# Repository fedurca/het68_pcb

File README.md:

# het68_pcb

Zadání a KiCad návrh PCB pro **het68** (akustická detekce dronů).

Aktuální verze: **[v4.9.0](https://github.com/fedurca/het68_pcb/releases/tag/v4.9.0)** — viz [CHANGELOG.md](CHANGELOG.md). Kusovník sady: [kicad/BOM_KIT.csv](kicad/BOM_KIT.csv). Po deskách: [kicad/BOM_v4.csv](kicad/BOM_v4.csv).

Firmware a geometrie pole: [fedurca/het68](https://github.com/fedurca/het68). Zadání: [docs/ZADANI_PCB.md](docs/ZADANI_PCB.md). Projekty v KiCadu: [kicad/README.md](kicad/README.md).

## Co to je

v4 je sada **Core 6L + vyměnitelná silová deska + šest satelitů**. Na měď nepřijde 230 V, 22 kV ani 110 kV.

**Core** (`kicad/het68-core`) nese nativní RP2350B, flash, PSRAM, USB-C, šest RJ45 s LVDS, piezo, env senzor, ADXL355, stavovou SK6812, tlačítka RESET / BOOT / USER a `J_MESH` na Heltec WiFi LoRa 32 V3 (868 MHz). MeshCore běží na Heltecu, takže uzel v síti žije, i když DSP spí. `WAKE_DSP` zapíná `+3V3_DIG`.

**Silová deska** má tři SKU se stejným interconnectem 2×10: NN (multiplex CT), VN (silnější GDT/TVS), VVN (harvest CT + Rogowski). Společný front-end je jen sekundár: GDT, TVS, LC, burden, crowbar, MPPT, článek 21700 (LiFePO4/LTO), 5 V a vždyživý `+3V3_RF`.

**Satelit** je šest destiček 6L. Ven z desky kouká jen akustický otvor T5848 a kruh **8× SK6812**. Tělo mikrofonu, RJ45 a ostatní elektronika jsou na druhé straně. Režim linky volí propojka na satelitu: diferenciální LVDS, jednostranných 3,3 V, nebo 1,8 V přímo na T5848. Mapa [`docs/PINOUT_SAT_v4.csv`](docs/PINOUT_SAT_v4.csv).

## Prototyp

Náhledy Core a satelitu jsou z v4.9.0. Ukazují svislý RJ45 a na zadní straně satelitu propojky režimu. Silová deska je náhled z v4.6.0.

Měď: [Core](docs/img/v490/core-top.svg) · [satelit ven](docs/img/v490/sat-front.svg) · [satelit zadek](docs/img/v490/sat-back.svg) · [silová](docs/img/v460/pwr-nn-top.svg). Maska venkovní strany satelitu: [SVG](docs/img/v490/sat-front-mask.svg). Schémata: [Core](docs/img/v490/core-sch.pdf) · [satelit](docs/img/v490/sat-sch.pdf) · [silová](docs/img/v460/pwr-nn-sch.pdf). Gerbery a nastavení formuláře: [`kicad/jlc/`](kicad/jlc/) · [NASTAVENI.md](kicad/jlc/NASTAVENI.md).

## Vyrobitelnost

Na měď nejde 230 V / 22 kV / 110 kV. Gerbery z `kicad-cli` v `kicad/*/fab/`. TPV: JLC / standardní výroba, ENIG na 6L, ≥ 0603, ne BGA. QFN-80 0,4 mm a LGA chtějí ENIG.

| Deska | Rozměr | ERC error | DRC | Objednat? |
|---|---|---|---|---|
| Core | 160 × 100 mm, 6L Faraday, ENIG | 0 | 0 zkratů, 0 mezer, 43 otevřených párů | ne |
| Satelit | 50 × 80 mm, 6L, ven jen LED a port | 0 | 0 zkratů, 19 otevřených párů (dva jsou rohy zemních zón) | ne, dokud nejsou dotažené jack, WS a OE |
| Silová NN/VN/VVN | 140 × 80 mm, 2L 70 µm | 0 | 0 zkratů, otevřené páry 30 / 36 / 26 | ne jako hotový zdroj |

Schémata jsou elektricky uzavřená (ERC 0 chyb). Core vrtá prokov 0,30/0,15 mm, což se do rozteče QFN 0,40 mm vejde, a L4 pod procesorem je plocha `+3V3_DIG`. DRC Core nemá zkrat ani mezeru. Otevřených je 43 párů. Část z nich je původní únik z prstence QFN, zbytek jsou vývody svislého RJ45 a stopy, které nová rozteč pinů přerušila. Satelit nemá zkrat. Vzdušné zůstávají `LED` a část `SD` u jacku, `OE`, krátká mezera `SD_3V3` u `U5` a sítě slovního taktu (`WS_LVDS`, `WS_P`, `WS_T`, `WS_N`). Dva záznamy jsou rohy zemních zón.

## VF / EMC (silné rušení)

- 6L Faraday: L2/L5 souvislá GND. Na Core je L4 jedna plocha `+3V3_DIG`. Silové desky mají L4 rozdělené. Stitch po obvodu.
- Diferenciální režim vozí I²S po LVDS (T568B páry). Propojka na satelitu umí i jednostranných 3,3 V a 1,8 V. Stínění je na GND na Core i na satelitu.
- CMC na SCK, WS i SD na obou koncích; nízko-kapacitní TVS napříč párem; 100 Ω u přijímače (SN65LVDS2 / SN65LVDS32 nemají vnitřní zakončení).
- Ferit 600 Ω na 3V3 každého jacku a na satelitu za PPTC.
- Krystal 12 MHz s C0G 15 pF (ne X7R 100 nF). Sériové 33 Ω na I²S u MCU, 22 Ω + ESD na UART MeshCore.
- Rádio (SX1262) je na Heltecu mimo DSP; `+3V3_RF` je vždyživé a oddělené od hradlovaného `+3V3_DIG`.

## Co je ještě potřeba

1. **Firmware.** DSP = RP2350B. MeshCore na Heltecu: `Heltec_lora32_v3`, UART GPIO5/6, WAKE GPIO7.
2. **Dokončit střední piny QFN-80** (QSPI SD2/SD3, část LED, SWD, UART) a zbylé LVDS páry. Silová deska má překryté pady z rozmístění.
3. **Heltec je lab.** ~40–80 mA. Stamp nRF52 později. LTO povinná, minimální SOC repeateru 30 %.
4. **110 kV.** Žádný externí kabel ze sféry. Anténa U.FL do slotu u stampu.
5. **RGB na 3,3 V.** Firmware svítí nejvýš dvěma pixely naráz.

## Sestava

Kleště / CT jsou na jednom izolovaném vodiči. Na desku jde jen sekundár (burden, LC, crowbar). Panel a článek LiFePO4/LTO jsou u silové desky, výstup `+5V_ALWAYS` jde na Core, šest satelitů je na RJ45.

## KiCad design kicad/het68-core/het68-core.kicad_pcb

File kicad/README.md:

# het68 — KiCad (v4.1.0)

Náhledy a kontext: [README](../README.md) repozitáře.

v4 kreslí **Core 6L**, tři silové SKU a satelit LVDS.

| Projekt | Deska | Vrstvy | Obrys |
|---|---|---|---|
| [het68-core](het68-core/het68-core.kicad_pro) | RP2350B + J_MESH Heltec V3 + 6× RJ45 LVDS | 6 Faraday | 160 × 100 mm |
| [het68-sat](het68-sat/het68-sat.kicad_pro) | satelit 6L LVDS + T5848 + 8× SK6812 | 6 Faraday, ENIG | 50 × 80 mm |
| [het68-pwr-nn](het68-pwr-nn/het68-pwr-nn.kicad_pro) | silová NN, multiplex CT | 2, 70 µm | 140 × 80 mm |
| [het68-pwr-vn](het68-pwr-vn/het68-pwr-vn.kicad_pro) | silová VN, 15KP | 2, 70 µm | 140 × 80 mm |
| [het68-pwr-vvn](het68-pwr-vvn/het68-pwr-vvn.kicad_pro) | silová VVN, Rogowski | 2, 70 µm | 140 × 80 mm |

Generátor: `kicad/tools/gen_v4.py` (Python z KiCadu). 6L stackup: `kicad/tools/route6.py`. Kusovník sady: [`BOM_KIT.csv`](BOM_KIT.csv).

## Zapojení Core

- RP2350B QFN-80, W25Q128 SOIC-8, APS6404L SOIC-8, USB-C, krystal 12 MHz + C0G 15 pF.
- `+3V3_DIG` a `+1V8_AUDIO` hradluje `WAKE_DSP` (Heltec GPIO7). `+5V_ALWAYS` / `+3V3_RF` vždyživé.
- `J_MESH` 1×8: GND, 5V, UART TX/RX (22 Ω + ESD), WAKE_DSP, DSP_AWAKE, RST NC, rezerva. Stamp DNP paralelně na pinech 1–6.
- Šest svislých RJ45, zástrčka kolmo z přední strany. Mapa [`docs/PINOUT_SAT_v4.csv`](../docs/PINOUT_SAT_v4.csv). CMC na SCK/WS/SD, 100 Ω u RX SD, ferit na 3V3.
- GPIO: [`docs/PINOUT.csv`](../docs/PINOUT.csv).
- Interconnect: [`docs/INTERCONNECT_v4.md`](../docs/INTERCONNECT_v4.md).
- L1 SMT+GND, L2 GND, L3 stripline, L4 souvislá `+3V3_DIG`, L5 GND, L6 pomalé+GND. Prokov 0,30/0,15 mm. Stitch po obvodu.

## Silová deska

Jen sekundár CT/Rogowski. GDT, TVS, LC, THT burden 100 Ω, crowbar ~25 V, USB-C lab, CN3791, LiFePO4, boost 5 V, LDO 3V3_RF, INA3221, PT1000. NN má MOSFET multiplex burdenu. VN 15KP. VVN Rogowski + MCP6001.

## Satelit

6L Faraday. RJ45 stojí ze zadní strany, osa zástrčky je kolmá k desce. Režim linky volí jedna vodorovná propojka. `JP_SCK`, `JP_WS` a `JP_SD` jsou hřebínky 2×3 na spodní straně, pin 1 (čtvercový) je severovýchodní. Severní řádek je diferenciální LVDS, prostřední je jednostranných 3,3 V přes `TXS0104E`, jižní je 1,8 V přímo na T5848. `JP_T*` jen u diferenciálního režimu (100 Ω). `JP_SDN` 1–2 je záporný vývod budiče, 2–3 dává zápornou žílu na zem. `JP_OE` se nasazuje jen v režimu 1,8 V a vypne překladač. T5848 zůstává na 1,62–1,98 V. Stínění RJ45 je na satelitu na GND. DRC desky je bez zkratů. Vzdušné zůstávají vývod `LED` a část `SD` u jacku, `OE`, krátká mezera `SD_3V3` u `U5`, `WS_LVDS`, `WS_P`, `WS_T` a `WS_N`. Náhled je v [`docs/img/v490/`](../docs/img/v490/). ENIG, ≥ 0603.

## Výroba

Gerbery z `kicad-cli pcb export gerbers` (ne `WriteDRCReport`). Core a satelit 6L ENIG u JLC. Silová 2L 70 µm.

v4.1.0: schémata elektricky uzavřená, BoM sady, 3D náhledy. Spoje 6L jsou v4.2.0.

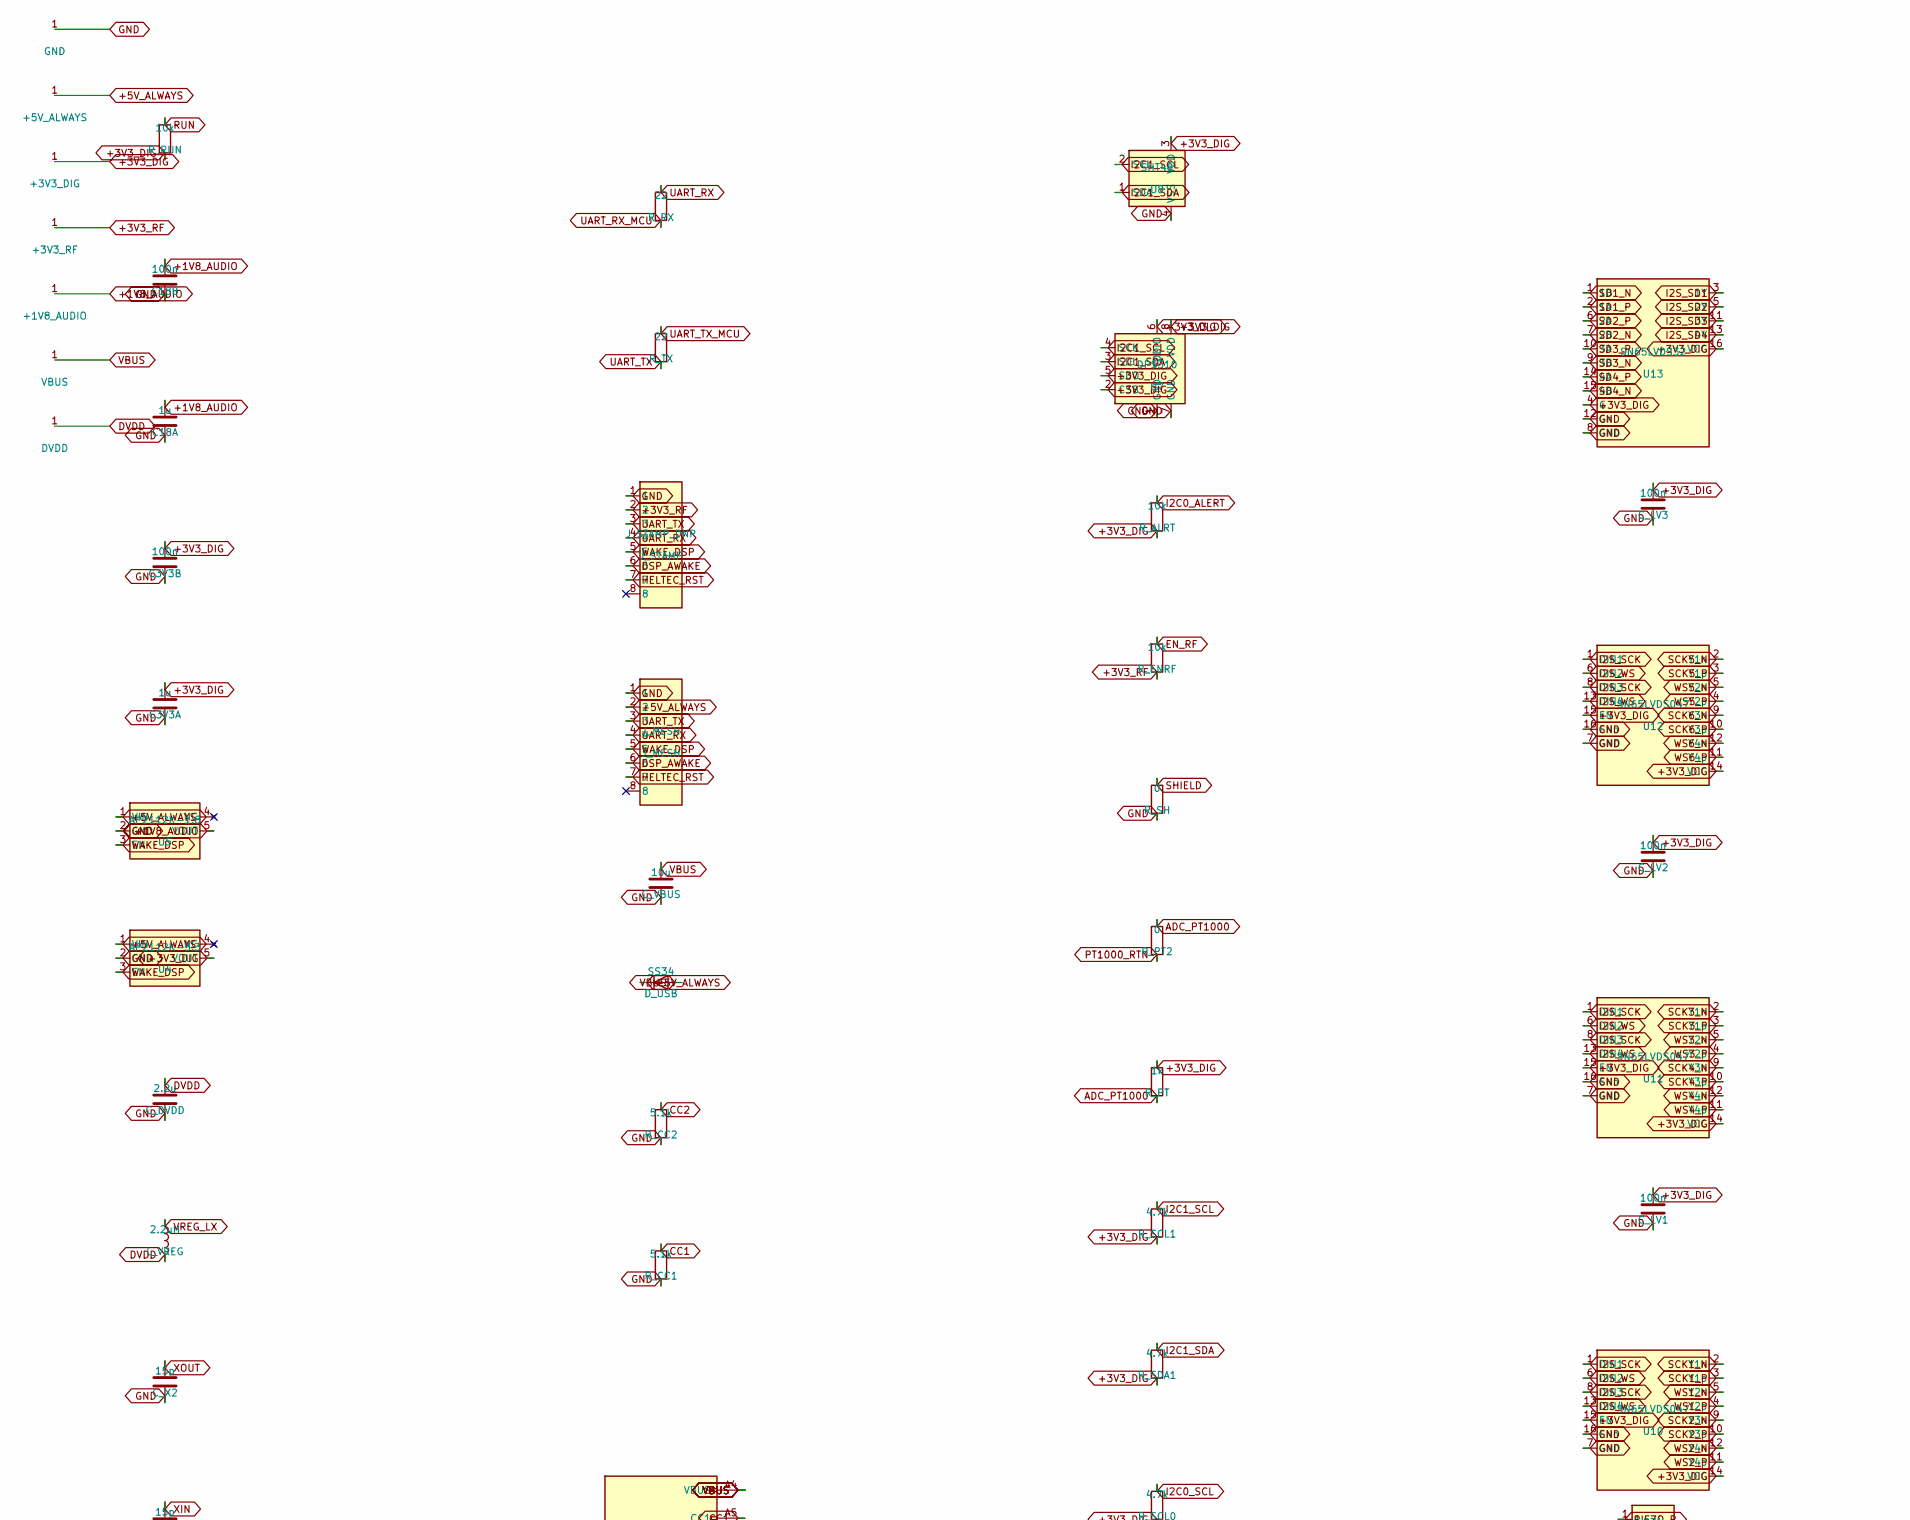
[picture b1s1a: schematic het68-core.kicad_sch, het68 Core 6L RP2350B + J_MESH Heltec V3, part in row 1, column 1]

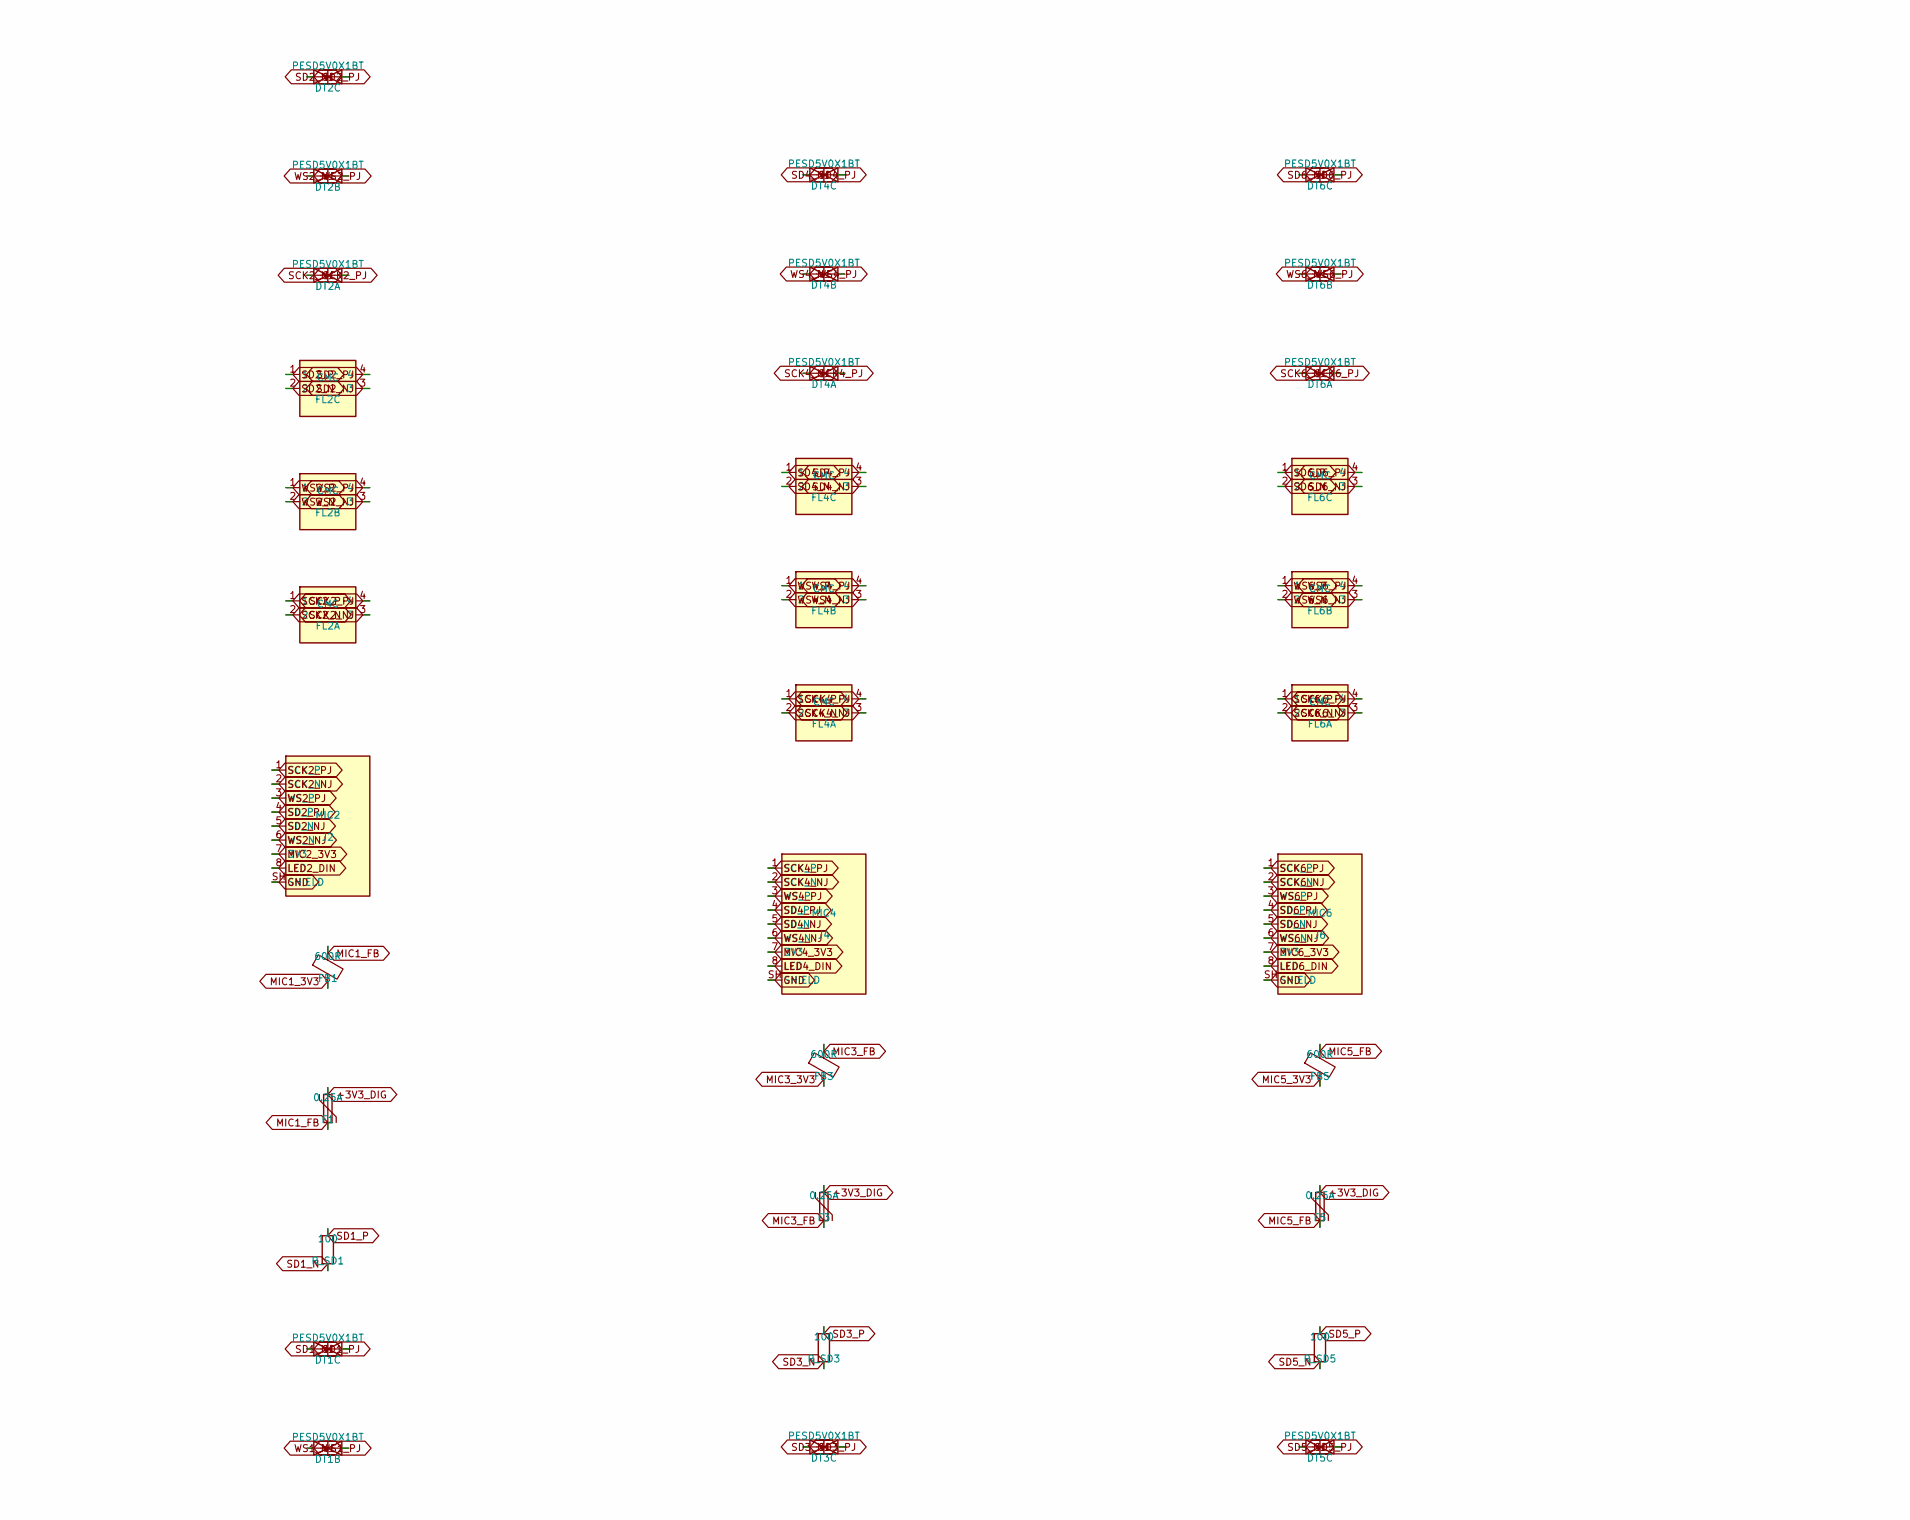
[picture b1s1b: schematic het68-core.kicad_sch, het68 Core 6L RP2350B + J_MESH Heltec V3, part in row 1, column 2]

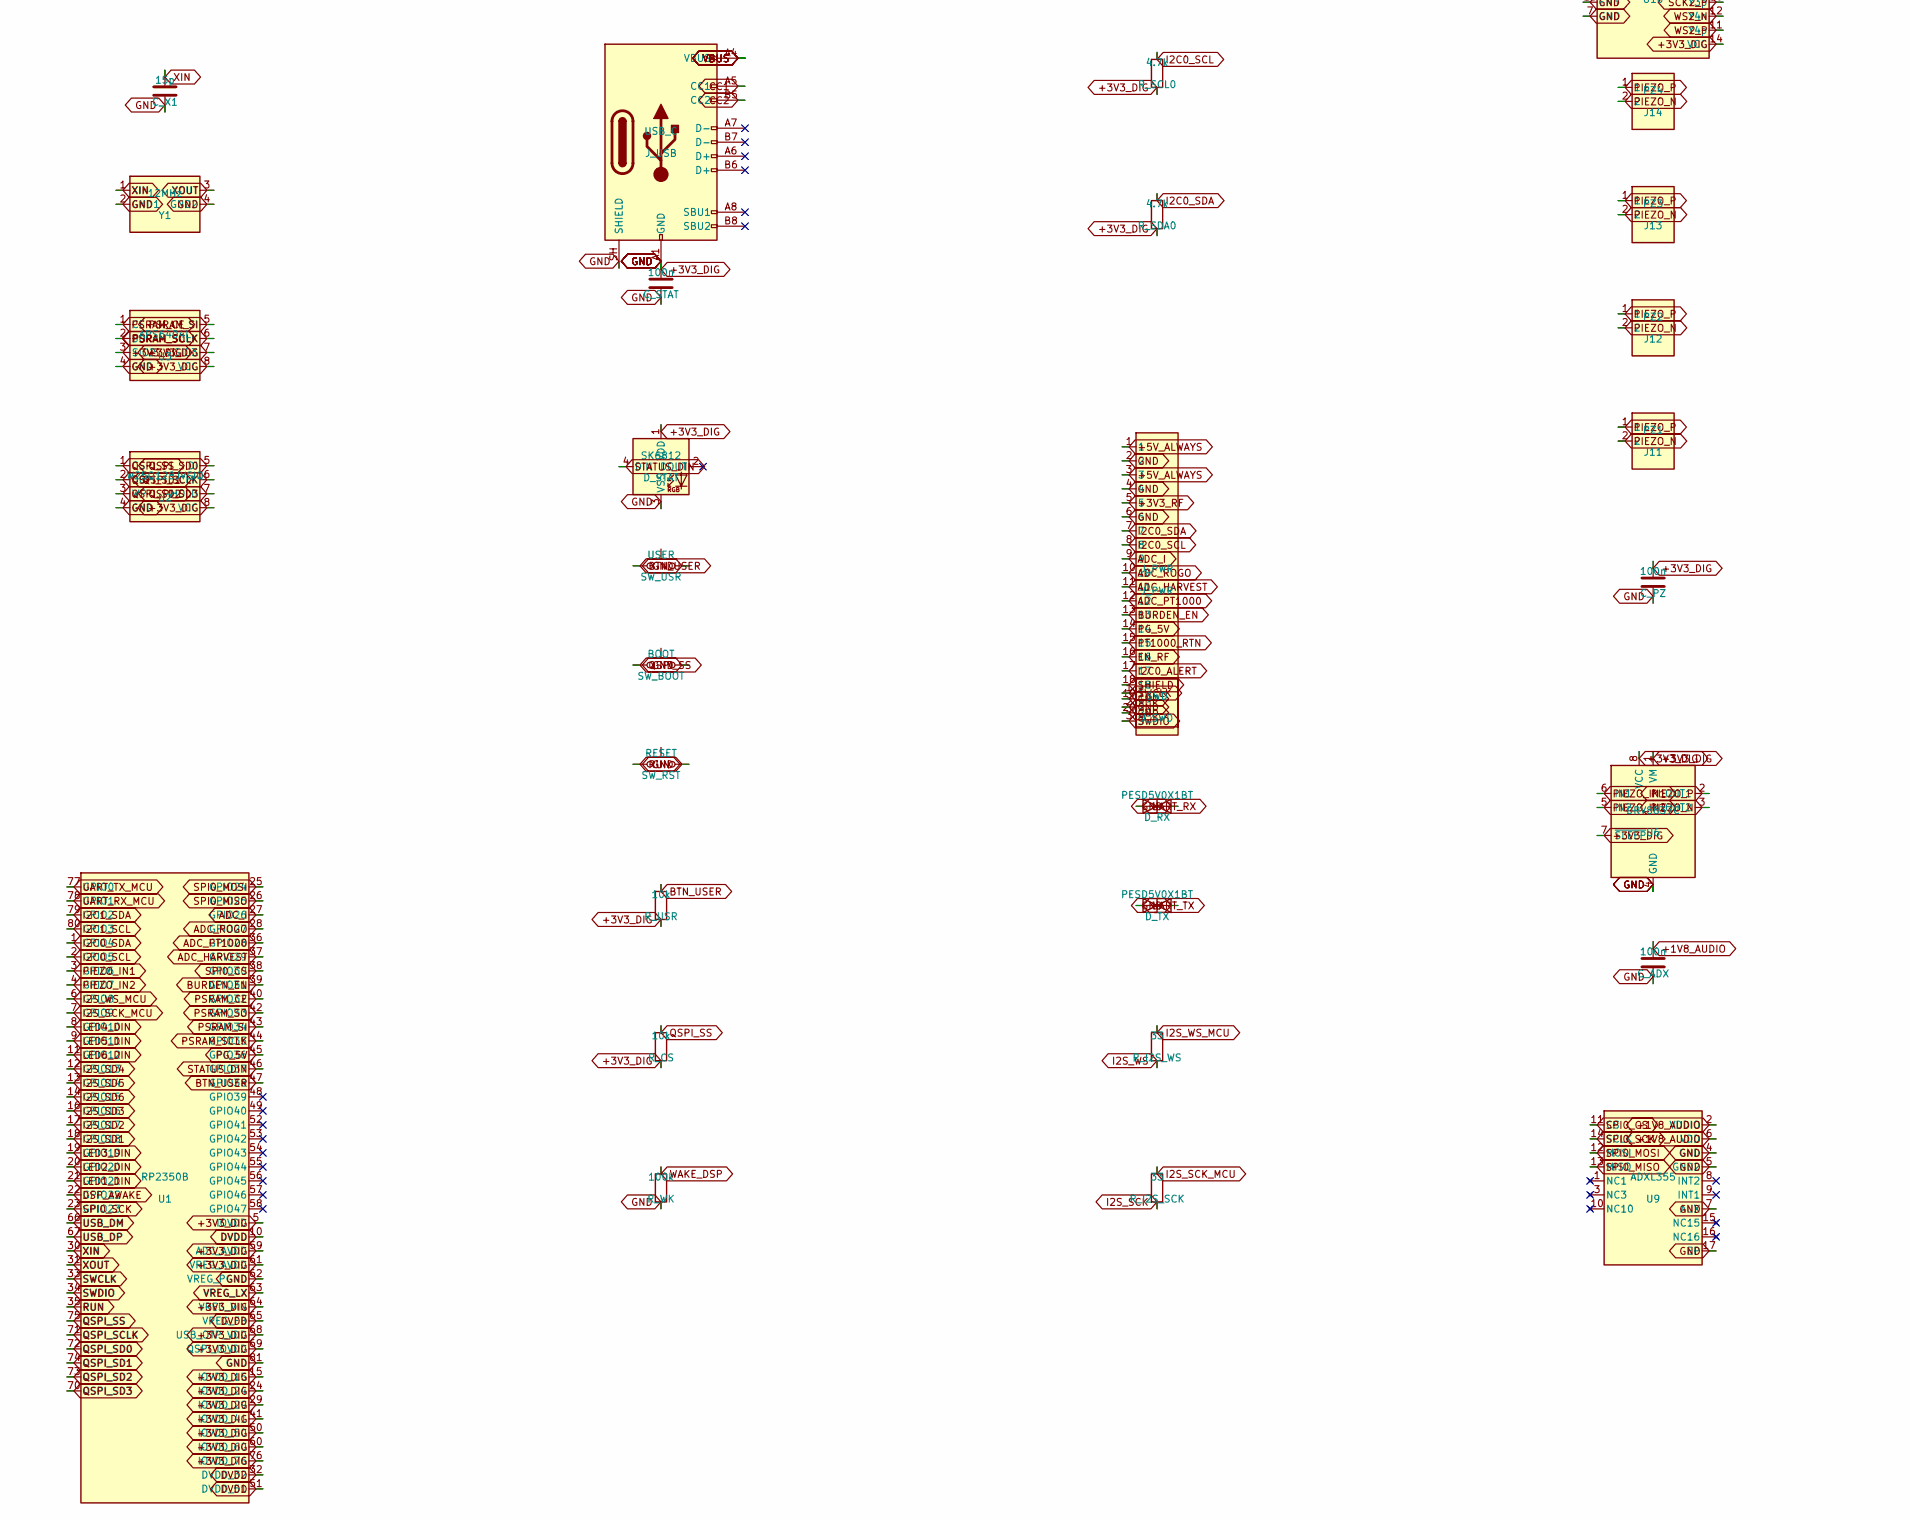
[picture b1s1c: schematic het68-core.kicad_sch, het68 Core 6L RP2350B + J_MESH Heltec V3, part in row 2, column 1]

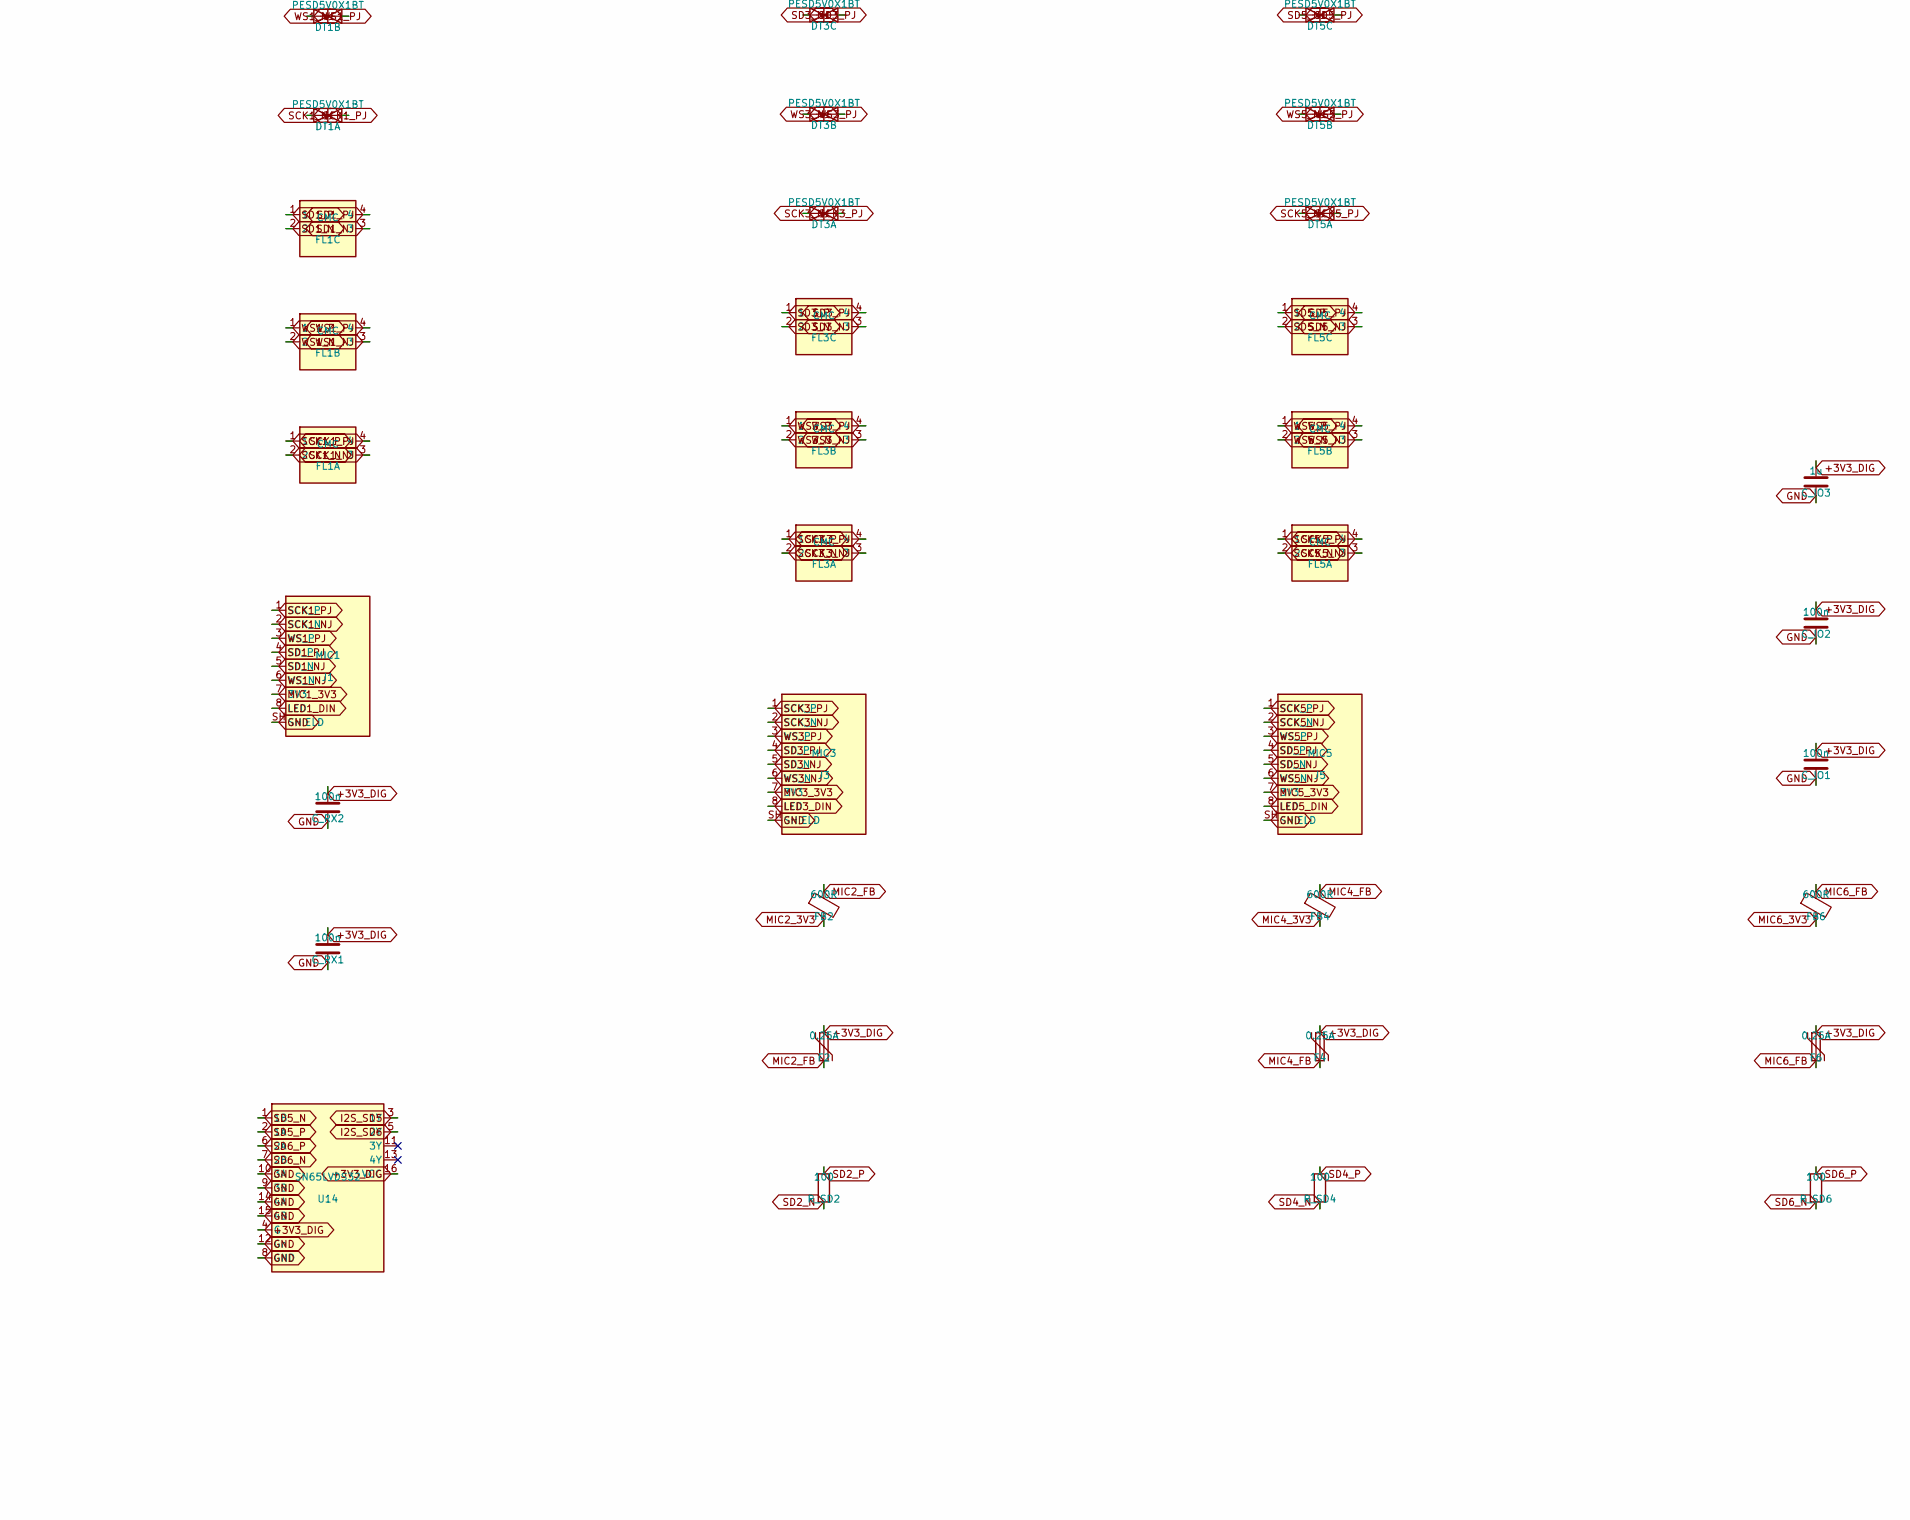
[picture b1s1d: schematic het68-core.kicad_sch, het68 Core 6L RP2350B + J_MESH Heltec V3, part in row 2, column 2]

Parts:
C3V3A, C18A: 1u; C_0603_1608Metric; MPN CL10A105KA8NNNC
C3V3B, C18B: 100n; C_0603_1608Metric; MPN CL10B104KB8NNNC
C_ADX: 100n; C_0603_1608Metric; MPN CL10B104KB8NNNC
C_DVDD: 2.2u; C_0805_2012Metric; MPN CL21A225KOQNNNE
C_IO1, C_IO2: 100n; C_0603_1608Metric; MPN CL10B104KB8NNNC
C_IO3: 1u; C_0603_1608Metric; MPN CL10A105KA8NNNC
C_LV1, C_LV2, C_LV3: 100n; C_0603_1608Metric; MPN CL10B104KB8NNNC
C_PZ: 100n; C_0603_1608Metric; MPN CL10B104KB8NNNC
C_RX1, C_RX2: 100n; C_0603_1608Metric; MPN CL10B104KB8NNNC
C_STAT: 100n; C_0603_1608Metric; MPN CL10B104KB8NNNC
C_VBUS: 10u; C_0805_2012Metric; MPN CL21A106KOQNNNE
C_X1, C_X2: 15p; C_0603_1608Metric; MPN CL10C150JB8NNNC
DT1A, DT1B, DT1C, DT2A, DT2B, DT2C, DT3A, DT3B, DT3C, DT4A, DT4B, DT4C, DT5A, DT5B, DT5C, DT6A, DT6B, DT6C: PESD5V0X1BT; D_SOD-323; MPN PESD5V0X1BT
D_RX: PESD5V0X1BT; D_SOD-323; MPN PESD5V0X1BT
D_STAT: SK6812; LED_WS2812B_PLCC4_5.0x5.0mm_P3.2mm; MPN SK6812 (5050, 3.3 V)
D_TX: PESD5V0X1BT; D_SOD-323; MPN PESD5V0X1BT
D_USB: SS34; D_SMC; MPN SS34
F1, F2, F3, F4, F5, F6: 0.25A; Fuse_0603_1608Metric; MPN PPTC 0603
FB1, FB2, FB3, FB4, FB5, FB6: 600R; L_0603_1608Metric; MPN BLM18PG601SN1D
FL1A, FL1B, FL1C, FL2A, FL2B, FL2C, FL3A, FL3B, FL3C, FL4A, FL4B, FL4C, FL5A, FL5B, FL5C, FL6A, FL6B, FL6C: CMC; L_CommonModeChoke_Coilank_ACM2012; MPN ACM2012
J1: MIC1; RJ45_Vertical_het68; MPN RJ45-8P8C-VERT
J2: MIC2; RJ45_Vertical_het68; MPN RJ45-8P8C-VERT
J3: MIC3; RJ45_Vertical_het68; MPN RJ45-8P8C-VERT
J4: MIC4; RJ45_Vertical_het68; MPN RJ45-8P8C-VERT
J5: MIC5; RJ45_Vertical_het68; MPN RJ45-8P8C-VERT
J6: MIC6; RJ45_Vertical_het68; MPN RJ45-8P8C-VERT
J11: PZ1; PinHeader_1x02_P2.54mm_Vertical; MPN PS1240
J12: PZ2; PinHeader_1x02_P2.54mm_Vertical; MPN PS1240
J13: PZ3; PinHeader_1x02_P2.54mm_Vertical; MPN PS1240
J14: PZ4; PinHeader_1x02_P2.54mm_Vertical; MPN PS1240
J_MESH: J_MESH; PinHeader_1x08_P2.54mm_Vertical; MPN PinHeader 1x8 Heltec V3
J_PWR: J_PWR; PinHeader_2x10_P2.54mm_Vertical; MPN interconnect 2x10
J_STAMP: J_STAMP_DNP; PinHeader_1x08_P2.54mm_Vertical; MPN DNP stamp RAK class
J_SWD: SWD; PinHeader_1x03_P2.54mm_Vertical; MPN SWD
J_USB: USB_C; USB_C_Receptacle_HRO_TYPE-C-31-M-12; MPN TYPE-C-31-M-12
L_VREG: 2.2uH; L_0805_2012Metric; MPN 2.2uH VREG
R_ALRT: 10k; R_0603_1608Metric; MPN RC0603FR-0710KL
R_CC1, R_CC2: 5.1k; R_0603_1608Metric; MPN RC0603FR-075K1L
R_CS: 10k; R_0603_1608Metric; MPN RC0603FR-0710KL
R_ENRF: 10k; R_0603_1608Metric; MPN RC0603FR-0710KL
R_I2S_SCK, R_I2S_WS: 33; R_0603_1608Metric; MPN RC0603FR-0733RL
R_PT: 1k; R_0603_1608Metric; MPN RC0603FR-071KL
R_PT2: 0; R_0603_1608Metric; MPN RC0603FR-070RL
R_RUN: 10k; R_0603_1608Metric; MPN RC0603FR-0710KL
R_RX: 22; R_0603_1608Metric; MPN RC0603FR-0722RL
R_SCL0, R_SCL1: 4.7k; R_0603_1608Metric; MPN RC0603FR-074K7L
R_SD1, R_SD2, R_SD3, R_SD4, R_SD5, R_SD6: 100; R_0603_1608Metric; MPN RC0603FR-07100RL
R_SDA0, R_SDA1: 4.7k; R_0603_1608Metric; MPN RC0603FR-074K7L
R_SH: 0; R_0603_1608Metric; MPN RC0603FR-070RL
R_TX: 22; R_0603_1608Metric; MPN RC0603FR-0722RL
R_USR: 10k; R_0603_1608Metric; MPN RC0603FR-0710KL
R_WK: 100k; R_0603_1608Metric; MPN RC0603FR-07100KL
SW_BOOT: BOOT; SW_SPST_PTS645Sx43SMTR92; MPN PTS645SM43SMTR92
SW_RST: RESET; SW_SPST_PTS645Sx43SMTR92; MPN PTS645SM43SMTR92
SW_USR: USER; SW_SPST_PTS645Sx43SMTR92; MPN PTS645SM43SMTR92
U1: RP2350B; QFN-80-1EP_10x10mm_P0.4mm_EP3.4x3.4mm_ThermalVias; MPN RP2350B
U2: W25Q128JVSIQ; SOIC-8_3.9x4.9mm_P1.27mm; MPN W25Q128JVSIQ
U3: APS6404L; SOIC-8_3.9x4.9mm_P1.27mm; MPN APS6404L-3SQR-SN
U4: AP2112K-3.3; SOT-23-5; MPN AP2112K-3.3TRG1
U5: AP2112K-1.8; SOT-23-5; MPN AP2112K-1.8TRG1
U6: DRV8837C; Texas_DSG0008A_WSON-8-1EP_2x2mm_P0.5mm_EP0.9x1.6mm; MPN DRV8837CDSGR
U7: DPS310; Bosch_LGA-8_2x2.5mm_P0.65mm_ClockwisePinNumbering; MPN DPS310
U8: SHT40; Sensirion_DFN-4_1.5x1.5mm_P0.8mm_SHT4x_NoCentralPad; MPN SHT40-AD1B-R2
U9: ADXL355; QFN-16-1EP_3x3mm_P0.5mm_EP1.7x1.7mm; MPN ADXL355BCCZ
U10, U11, U12: SN65LVDS047; TSSOP-16_4.4x5mm_P0.65mm; MPN SN65LVDS047PW
U13, U14: SN65LVDS32; SOIC-16_3.9x9.9mm_P1.27mm; MPN SN65LVDS32D
Y1: 12MHz; Crystal_SMD_3225-4Pin_3.2x2.5mm; MPN 12MHz 3225

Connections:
+1V8_AUDIO: C18A.1, C18B.1, C_ADX.1, U5.5 (VOUT), U9.2 (VDDIO), U9.6 (VDD)
+3V3_DIG: C3V3A.1, C3V3B.1, C_IO1.1, C_IO2.1, C_IO3.1, C_LV1.1, C_LV2.1, C_LV3.1, C_PZ.1, C_RX1.1, C_RX2.1, C_STAT.1, D_STAT.1 (VDD), F1.1, F2.1, F3.1, F4.1, F5.1, F6.1, R_ALRT.2, R_CS.2, R_PT.1, R_RUN.2, R_SCL0.2, R_SCL1.2, R_SDA0.2, R_SDA1.2, R_USR.2, U1.5 (IOVDD), U1.15 (IOVDD_15), U1.24 (IOVDD_24), U1.29 (IOVDD_29), U1.41 (IOVDD_41), U1.50 (IOVDD_50), U1.59 (ADC_AVDD), U1.60 (IOVDD_60), U1.61 (VREG_AVDD), U1.64 (VREG_VIN), U1.68 (USB_OTP_VDD), U1.69 (QSPI_IOVDD), U1.76 (IOVDD_76), U2.8 (VCC), U3.3 (SIO2), U3.7 (SIO3), U3.8 (VCC), U4.5 (VOUT), U6.1 (VM), U6.7 (~SLEEP), U6.8 (VCC), U7.2 (CSB), U7.5 (SDO), U7.6 (VDDIO), U7.8 (VDD), U8.3 (VDD), U10.14 (VCC), U10.15 (EN), U11.14 (VCC), U11.15 (EN), U12.14 (VCC), U12.15 (EN), U13.4 (G), U13.16 (VCC), U14.4 (G), U14.16 (VCC)
+3V3_RF: J_PWR.5, J_STAMP.2, R_ENRF.2
+5V_ALWAYS: D_USB.1 (K), J_MESH.2, J_PWR.1, J_PWR.3, U4.1 (VIN), U5.1 (VIN)
ADC_HARVEST: J_PWR.11, U1.37 (GPIO29)
ADC_I: J_PWR.9, U1.27 (GPIO26)
ADC_PT1000: J_PWR.12, R_PT.2, R_PT2.1, U1.36 (GPIO28)
ADC_ROGO: J_PWR.10, U1.28 (GPIO27)
BTN_USER: R_USR.1, SW_USR.1, U1.47 (GPIO38)
BURDEN_EN: J_PWR.13, U1.39 (GPIO31)
CC1: J_USB.A5 (CC1), R_CC1.1
CC2: J_USB.B5 (CC2), R_CC2.1
DSP_AWAKE: J_MESH.6, J_STAMP.6, U1.22 (GPIO22)
DVDD: C_DVDD.1, L_VREG.2, U1.10 (DVDD), U1.32 (DVDD_32), U1.51 (DVDD_51), U1.65 (VREG_FB)
EN_RF: J_PWR.16, R_ENRF.1
GND: C3V3A.2, C3V3B.2, C18A.2, C18B.2, C_ADX.2, C_DVDD.2, C_IO1.2, C_IO2.2, C_IO3.2, C_LV1.2, C_LV2.2, C_LV3.2, C_PZ.2, C_RX1.2, C_RX2.2, C_STAT.2, C_VBUS.2, C_X1.2, C_X2.2, D_RX.2 (A2), D_STAT.3 (VSS), D_TX.2 (A2), J1.SH (SHIELD), J2.SH (SHIELD), J3.SH (SHIELD), J4.SH (SHIELD), J5.SH (SHIELD), J6.SH (SHIELD), J_MESH.1, J_PWR.2, J_PWR.4, J_PWR.6, J_PWR.19, J_PWR.20, J_STAMP.1, J_SWD.2, J_USB.A1 (GND), J_USB.A12 (GND), J_USB.B1 (GND), J_USB.B12 (GND), J_USB.SH (SHIELD), R_CC1.2, R_CC2.2, R_SH.2, R_WK.2, SW_BOOT.2, SW_RST.2, SW_USR.2, U1.62 (VREG_PGND), U1.81 (GND), U2.4 (GND), U3.4 (GND), U4.2 (GND), U5.2 (GND), U6.4 (GND), U6.9 (GND), U7.1 (GND), U7.7 (GND), U8.4 (VSS), U9.4 (GND), U9.5 (GND2), U9.7 (AUX), U9.17 (EP), U10.7 (GND), U10.16 (ENn), U11.7 (GND), U11.16 (ENn), U12.7 (GND), U12.16 (ENn), U13.8 (GND), U13.12 (Gn), U14.8 (GND), U14.9 (3B), U14.10 (3A), U14.12 (Gn), U14.14 (4A), U14.15 (4B), Y1.2 (GND1), Y1.4 (GND2)
HELTEC_RST: J_MESH.7, J_STAMP.7
I2C0_ALERT: J_PWR.17, R_ALRT.1
I2C0_SCL: J_PWR.8, R_SCL0.1, U1.2 (GPIO5)
I2C0_SDA: J_PWR.7, R_SDA0.1, U1.1 (GPIO4)
I2C1_SCL: R_SCL1.1, U1.80 (GPIO3), U7.4 (SCK), U8.2 (SCL)
I2C1_SDA: R_SDA1.1, U1.79 (GPIO2), U7.3 (SDI), U8.1 (SDA)
I2S_SCK: R_I2S_SCK.2, U10.1 (DIN1), U10.8 (DIN3), U11.1 (DIN1), U11.8 (DIN3), U12.1 (DIN1), U12.8 (DIN3)
I2S_SCK_MCU: R_I2S_SCK.1, U1.7 (GPIO9)
I2S_SD1: U1.18 (GPIO18), U13.3 (1Y)
I2S_SD2: U1.17 (GPIO17), U13.5 (2Y)
I2S_SD3: U1.16 (GPIO16), U13.11 (3Y)
I2S_SD4: U1.12 (GPIO13), U13.13 (4Y)
I2S_SD5: U1.13 (GPIO14), U14.3 (1Y)
I2S_SD6: U1.14 (GPIO15), U14.5 (2Y)
I2S_WS: R_I2S_WS.2, U10.6 (DIN2), U10.13 (DIN4), U11.6 (DIN2), U11.13 (DIN4), U12.6 (DIN2), U12.13 (DIN4)
I2S_WS_MCU: R_I2S_WS.1, U1.6 (GPIO8)
LED1_DIN: J1.8 (LED), U1.21 (GPIO21)
LED2_DIN: J2.8 (LED), U1.20 (GPIO20)
LED3_DIN: J3.8 (LED), U1.19 (GPIO19)
LED4_DIN: J4.8 (LED), U1.8 (GPIO10)
LED5_DIN: J5.8 (LED), U1.9 (GPIO11)
LED6_DIN: J6.8 (LED), U1.11 (GPIO12)
MIC1_3V3: FB1.2, J1.7 (3V3)
MIC1_FB: F1.2, FB1.1
MIC2_3V3: FB2.2, J2.7 (3V3)
MIC2_FB: F2.2, FB2.1
MIC3_3V3: FB3.2, J3.7 (3V3)
MIC3_FB: F3.2, FB3.1
MIC4_3V3: FB4.2, J4.7 (3V3)
MIC4_FB: F4.2, FB4.1
MIC5_3V3: FB5.2, J5.7 (3V3)
MIC5_FB: F5.2, FB5.1
MIC6_3V3: FB6.2, J6.7 (3V3)
MIC6_FB: F6.2, FB6.1
PG_5V: J_PWR.14, U1.45 (GPIO36)
PIEZO_IN1: U1.3 (GPIO6), U6.6 (IN1)
PIEZO_IN2: U1.4 (GPIO7), U6.5 (IN2)
PIEZO_N: J11.2, J12.2, J13.2, J14.2, U6.3 (OUT2)
PIEZO_P: J11.1, J12.1, J13.1, J14.1, U6.2 (OUT1)
PSRAM_CE: U1.40 (GPIO32), U3.1 (CE)
PSRAM_SCLK: U1.44 (GPIO35), U3.6 (SCLK)
PSRAM_SI: U1.43 (GPIO34), U3.5 (SI)
PSRAM_SO: U1.42 (GPIO33), U3.2 (SO)
PT1000_RTN: J_PWR.15, R_PT2.2
QSPI_SCLK: U1.71 (QSPI_SCLK), U2.6 (CLK)
QSPI_SD0: U1.72 (QSPI_SD0), U2.5 (DI)
QSPI_SD1: U1.74 (QSPI_SD1), U2.2 (DO)
QSPI_SD2: U1.73 (QSPI_SD2), U2.3 (WP)
QSPI_SD3: U1.70 (QSPI_SD3), U2.7 (HOLD)
QSPI_SS: R_CS.1, SW_BOOT.1, U1.75 (QSPI_SS), U2.1 (CS)
RUN: R_RUN.1, SW_RST.1, U1.35 (RUN)
SCK1_N: FL1A.2, U10.2 (Y1n)
SCK1_NJ: DT1A.2 (A2), FL1A.3, J1.2 (SCK_N)
SCK1_P: FL1A.1, U10.3 (Y1p)
SCK1_PJ: DT1A.1 (A1), FL1A.4, J1.1 (SCK_P)
SCK2_N: FL2A.2, U10.9 (Y3n)
SCK2_NJ: DT2A.2 (A2), FL2A.3, J2.2 (SCK_N)
SCK2_P: FL2A.1, U10.10 (Y3p)
SCK2_PJ: DT2A.1 (A1), FL2A.4, J2.1 (SCK_P)
SCK3_N: FL3A.2, U11.2 (Y1n)
SCK3_NJ: DT3A.2 (A2), FL3A.3, J3.2 (SCK_N)
SCK3_P: FL3A.1, U11.3 (Y1p)
SCK3_PJ: DT3A.1 (A1), FL3A.4, J3.1 (SCK_P)
SCK4_N: FL4A.2, U11.9 (Y3n)
SCK4_NJ: DT4A.2 (A2), FL4A.3, J4.2 (SCK_N)
SCK4_P: FL4A.1, U11.10 (Y3p)
SCK4_PJ: DT4A.1 (A1), FL4A.4, J4.1 (SCK_P)
SCK5_N: FL5A.2, U12.2 (Y1n)
SCK5_NJ: DT5A.2 (A2), FL5A.3, J5.2 (SCK_N)
SCK5_P: FL5A.1, U12.3 (Y1p)
SCK5_PJ: DT5A.1 (A1), FL5A.4, J5.1 (SCK_P)
SCK6_N: FL6A.2, U12.9 (Y3n)
SCK6_NJ: DT6A.2 (A2), FL6A.3, J6.2 (SCK_N)
SCK6_P: FL6A.1, U12.10 (Y3p)
SCK6_PJ: DT6A.1 (A1), FL6A.4, J6.1 (SCK_P)
SD1_N: FL1C.2, R_SD1.2, U13.1 (1B)
SD1_NJ: DT1C.2 (A2), FL1C.3, J1.5 (SD_N)
SD1_P: FL1C.1, R_SD1.1, U13.2 (1A)
SD1_PJ: DT1C.1 (A1), FL1C.4, J1.4 (SD_P)
SD2_N: FL2C.2, R_SD2.2, U13.7 (2B)
SD2_NJ: DT2C.2 (A2), FL2C.3, J2.5 (SD_N)
SD2_P: FL2C.1, R_SD2.1, U13.6 (2A)
SD2_PJ: DT2C.1 (A1), FL2C.4, J2.4 (SD_P)
SD3_N: FL3C.2, R_SD3.2, U13.9 (3B)
SD3_NJ: DT3C.2 (A2), FL3C.3, J3.5 (SD_N)
SD3_P: FL3C.1, R_SD3.1, U13.10 (3A)
SD3_PJ: DT3C.1 (A1), FL3C.4, J3.4 (SD_P)
SD4_N: FL4C.2, R_SD4.2, U13.15 (4B)
SD4_NJ: DT4C.2 (A2), FL4C.3, J4.5 (SD_N)
SD4_P: FL4C.1, R_SD4.1, U13.14 (4A)
SD4_PJ: DT4C.1 (A1), FL4C.4, J4.4 (SD_P)
SD5_N: FL5C.2, R_SD5.2, U14.1 (1B)
SD5_NJ: DT5C.2 (A2), FL5C.3, J5.5 (SD_N)
SD5_P: FL5C.1, R_SD5.1, U14.2 (1A)
SD5_PJ: DT5C.1 (A1), FL5C.4, J5.4 (SD_P)
SD6_N: FL6C.2, R_SD6.2, U14.7 (2B)
SD6_NJ: DT6C.2 (A2), FL6C.3, J6.5 (SD_N)
SD6_P: FL6C.1, R_SD6.1, U14.6 (2A)
SD6_PJ: DT6C.1 (A1), FL6C.4, J6.4 (SD_P)
SHIELD: J_PWR.18, R_SH.1
SPI0_CS: U1.38 (GPIO30), U9.11 (CS)
SPI0_MISO: U1.26 (GPIO25), U9.13 (MISO)
SPI0_MOSI: U1.25 (GPIO24), U9.12 (MOSI)
SPI0_SCK: U1.23 (GPIO23), U9.14 (SCLK)
STATUS_DIN: D_STAT.4 (DIN), U1.46 (GPIO37)
SWCLK: J_SWD.1, U1.33 (SWCLK)
SWDIO: J_SWD.3, U1.34 (SWDIO)
UART_RX: D_RX.1 (A1), J_MESH.4, J_STAMP.4, R_RX.1
UART_RX_MCU: R_RX.2, U1.78 (GPIO1)
UART_TX: D_TX.1 (A1), J_MESH.3, J_STAMP.3, R_TX.2
UART_TX_MCU: R_TX.1, U1.77 (GPIO0)
USB_DM: U1.66 (USB_DM)
USB_DP: U1.67 (USB_DP)
VBUS: C_VBUS.1, D_USB.2 (A), J_USB.A4 (VBUS), J_USB.A9 (VBUS), J_USB.B4 (VBUS), J_USB.B9 (VBUS)
VREG_LX: L_VREG.1, U1.63 (VREG_LX)
WAKE_DSP: J_MESH.5, J_STAMP.5, R_WK.1, U4.3 (EN), U5.3 (EN)
WS1_N: FL1B.2, U10.5 (Y2n)
WS1_NJ: DT1B.2 (A2), FL1B.3, J1.6 (WS_N)
WS1_P: FL1B.1, U10.4 (Y2p)
WS1_PJ: DT1B.1 (A1), FL1B.4, J1.3 (WS_P)
WS2_N: FL2B.2, U10.12 (Y4n)
WS2_NJ: DT2B.2 (A2), FL2B.3, J2.6 (WS_N)
WS2_P: FL2B.1, U10.11 (Y4p)
WS2_PJ: DT2B.1 (A1), FL2B.4, J2.3 (WS_P)
WS3_N: FL3B.2, U11.5 (Y2n)
WS3_NJ: DT3B.2 (A2), FL3B.3, J3.6 (WS_N)
WS3_P: FL3B.1, U11.4 (Y2p)
WS3_PJ: DT3B.1 (A1), FL3B.4, J3.3 (WS_P)
WS4_N: FL4B.2, U11.12 (Y4n)
WS4_NJ: DT4B.2 (A2), FL4B.3, J4.6 (WS_N)
WS4_P: FL4B.1, U11.11 (Y4p)
WS4_PJ: DT4B.1 (A1), FL4B.4, J4.3 (WS_P)
WS5_N: FL5B.2, U12.5 (Y2n)
WS5_NJ: DT5B.2 (A2), FL5B.3, J5.6 (WS_N)
WS5_P: FL5B.1, U12.4 (Y2p)
WS5_PJ: DT5B.1 (A1), FL5B.4, J5.3 (WS_P)
WS6_N: FL6B.2, U12.12 (Y4n)
WS6_NJ: DT6B.2 (A2), FL6B.3, J6.6 (WS_N)
WS6_P: FL6B.1, U12.11 (Y4p)
WS6_PJ: DT6B.1 (A1), FL6B.4, J6.3 (WS_P)
XIN: C_X1.1, U1.30 (XIN), Y1.1 (XIN)
XOUT: C_X2.1, U1.31 (XOUT), Y1.3 (XOUT)
